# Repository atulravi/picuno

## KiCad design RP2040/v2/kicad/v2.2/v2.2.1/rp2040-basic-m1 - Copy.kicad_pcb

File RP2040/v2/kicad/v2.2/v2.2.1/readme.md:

Added India Flag under Flash. Our commitment to Made IN India. Also minor changes. <br>
Also removed 2 logic level changers since cruicial RX TX pins for BLE etc were getting blocked. Not considering replacing it for all pins. <br>
Since 3.3V inputs will be level shifted to 5V. Inputs are not allowed on GPIOs 2-6. Others are perfectly fine. <br>
Qwiic added. Logos added.

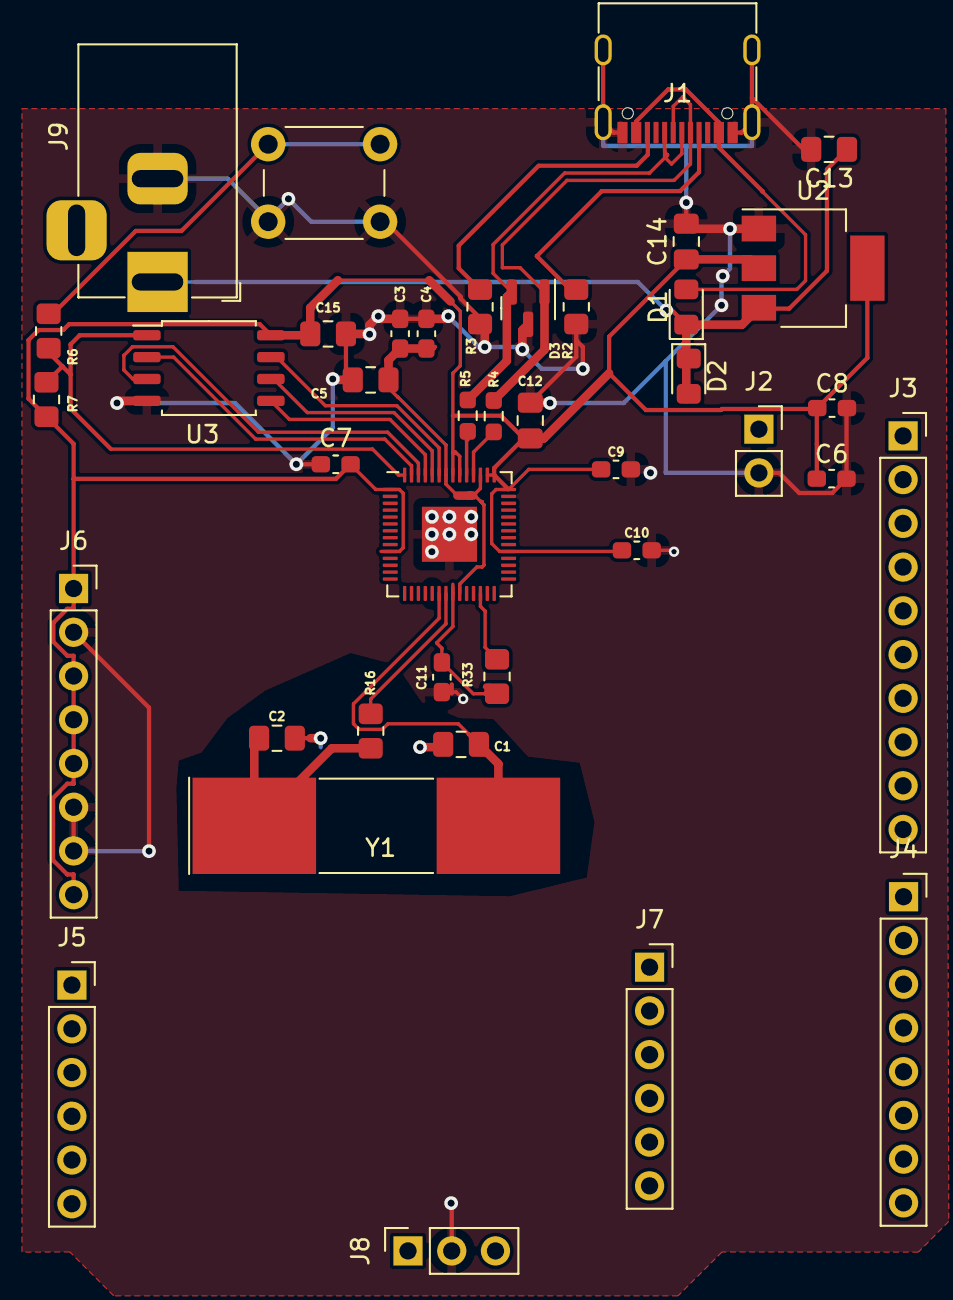
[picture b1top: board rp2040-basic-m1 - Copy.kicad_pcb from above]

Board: 2 copper layers, 40 parts (0 on the bottom side), 55 nets.

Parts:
C1, C2: 27p; C_0805_2012Metric_Pad1.18x1.45mm_HandSolder
C3, C4, C6, C7, C8, C9, C10, C11: 100n; C_0603_1608Metric_Pad1.08x0.95mm_HandSolder
C5, C12: 1u; C_0805_2012Metric_Pad1.18x1.45mm_HandSolder
C13, C14: 10u; C_0805_2012Metric_Pad1.18x1.45mm_HandSolder
C15: 100n; C_0805_2012Metric_Pad1.18x1.45mm_HandSolder
D1, D2: D_Schottky; D_0805_2012Metric_Pad1.15x1.40mm_HandSolder
D3: D_TVS_Dual_AAC; SOT-23
J1: USB_C_Receptacle_USB2.0; USB_C_Receptacle_G-Switch_GT-USB-7010ASV
J2: Conn_01x02_Pin; PinSocket_1x02_P2.54mm_Vertical
J3: Conn_01x10_Socket; PinSocket_1x10_P2.54mm_Vertical
J4, J6: Conn_01x08_Socket; PinSocket_1x08_P2.54mm_Vertical
J5: Conn_01x06_Pin; PinSocket_1x06_P2.54mm_Vertical
J7: Conn_01x06_Socket; PinSocket_1x06_P2.54mm_Vertical
J8: Conn_01x03_Pin; PinSocket_1x03_P2.54mm_Vertical
J9: Barrel_Jack_Switch; BarrelJack_Horizontal
R2, R3, R33: 5.1K; R_0805_2012Metric_Pad1.20x1.40mm_HandSolder
R4, R5: 27R; R_0603_1608Metric_Pad0.98x0.95mm_HandSolder
R6, R16: 1k; R_0805_2012Metric_Pad1.20x1.40mm_HandSolder
R7: 10k; R_0805_2012Metric_Pad1.20x1.40mm_HandSolder
SW2: TACT SW; SW_PUSH_6mm_H8.5mm
U1: RP2040; QFN-56-1EP_7x7mm_P0.4mm_EP3.2x3.2mm
U2: AZ1117CH-3.3TRG1 SOT223-3; SOT-223-3_TabPin2
U3: W25Q128JVS; SOIC-8_5.23x5.23mm_P1.27mm
Y1: Crystal 12 Mhz; Crystal_SMD_SeikoEpson_MA505-2Pin_12.7x5.1mm_HandSoldering

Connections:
+1V1: C3.1, C4.1, C5.1, U1.23 (DVDD), U1.45 (VREG_VOUT), U1.50 (DVDD)
+3.3V: C6.1, C7.1, C8.1, C9.1, C10.1, C11.1, C12.1, C14.1, C15.1, J6.1, J6.3, J6.4, J6.5, J6.8, R7.1, R33.1, U1.1 (IOVDD), U1.10 (IOVDD), U1.22 (IOVDD), U1.33 (IOVDD), U1.42 (IOVDD), U1.43 (ADC_AVDD), U1.44 (VREG_IN), U1.48 (USB_VDD), U1.49 (IOVDD), U2.2 (VO), U3.8 (VCC)
/USB1_DN: D3.1 (A1), J1.A7 (D-), J1.B7 (D-), R4.1
/USB1_DP: D3.2 (A2), J1.A6 (D+), J1.B6 (D+), R5.1
GND: C1.1, C2.1, C3.2, C4.2, C5.2, C6.2, C7.2, C8.2, C9.2, C10.2, C11.2, C12.2, C13.2, C14.2, C15.2, D3.3 (common), J1.A1 (GND), J1.A12 (GND), J1.B1 (GND), J1.B12 (GND), J1.S1 (SHIELD), J2.2, J6.2, J6.6, J6.7, J8.2, J9.2, R2.2, R3.2, SW2.2, U1.19 (TESTEN), U1.57 (GND), U2.1 (GND), U3.4 (GND)
unnamed: C2.2, R16.1, Y1.1
unnamed: D1.2 (A), J1.A4 (VBUS), J1.A9 (VBUS), J1.B4 (VBUS), J1.B9 (VBUS)
unnamed: D2.2 (A), J2.1
unnamed: J1.A5 (CC1), R2.1
unnamed: J1.B5 (CC2), R3.1
unnamed: J3.1, U1.11 (GPIO8)
unnamed: J3.2, U1.12 (GPIO9)
unnamed: J3.3, U1.13 (GPIO10)
unnamed: J3.4, U1.14 (GPIO11)
unnamed: J3.5, U1.15 (GPIO12)
unnamed: J3.6, U1.16 (GPIO13)
unnamed: J3.7, U1.17 (GPIO14)
unnamed: J3.8, U1.18 (GPIO15)
unnamed: J3.9, U1.27 (GPIO16)
unnamed: J3.10, U1.28 (GPIO17)
unnamed: J4.1, U1.2 (GPIO0)
unnamed: J4.2, U1.3 (GPIO1)
unnamed: J4.3, U1.4 (GPIO2)
unnamed: J4.4, U1.5 (GPIO3)
unnamed: J4.5, U1.6 (GPIO4)
unnamed: J4.6, U1.7 (GPIO5)
unnamed: J4.7, U1.8 (GPIO6)
unnamed: J4.8, U1.9 (GPIO7)
unnamed: J5.1, U1.36 (GPIO24)
unnamed: J5.2, U1.37 (GPIO25)
unnamed: J5.3, U1.38 (GPIO26_ADC0)
unnamed: J5.4, U1.39 (GPIO27_ADC1)
unnamed: J5.5, U1.40 (GPIO28_ADC2)
unnamed: J5.6, U1.41 (GPIO29_ADC3)
unnamed: J7.1, U1.29 (GPIO18)
unnamed: J7.2, U1.30 (GPIO19)
unnamed: J7.3, U1.31 (GPIO20)
unnamed: J7.4, U1.32 (GPIO21)
unnamed: J7.5, U1.34 (GPIO22)
unnamed: J7.6, U1.35 (GPIO23)
unnamed: J8.1, U1.24 (SWCLK)
unnamed: J8.3, U1.25 (SWD)
unnamed: R6.1, SW2.1
unnamed: R33.2, U1.26 (RUN)
unnamed: C1.2, U1.20 (XIN), Y1.2
unnamed: R16.2, U1.21 (XOUT)
QSPI_SCLK: U1.52 (QSPI_SCLK), U3.6 (CLK)
QSPI_SD0: U1.53 (QSPI_SD0), U3.5 (DI(IO0))
QSPI_SD2: U1.54 (QSPI_SD2), U3.3 (IO2)
QSPI_SD3: U1.51 (QSPI_SD3), U3.7 (IO3)
QSPI_SS: R6.2, R7.2, U1.56 (QSPI_SS), U3.1 (~CS)
QSPI_SSD1: U1.55 (QSPI_SD1), U3.2 (DO(IO1))
USB_DN: R4.2, U1.46 (USB_DM)
USB_DP: R5.2, U1.47 (USB_DP)
VBUS: C13.1, D1.1 (K), D2.1 (K), J9.1, U2.3 (VI)
